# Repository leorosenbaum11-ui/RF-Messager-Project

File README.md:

# RF-Messager-Project
Radio Project using Micrf110ymm and Micrf220ayqs to recieve and transmit character data to an LCD screen. Working on code(Python), and fabrication. Also working on integrated or USB keyboard functionality.

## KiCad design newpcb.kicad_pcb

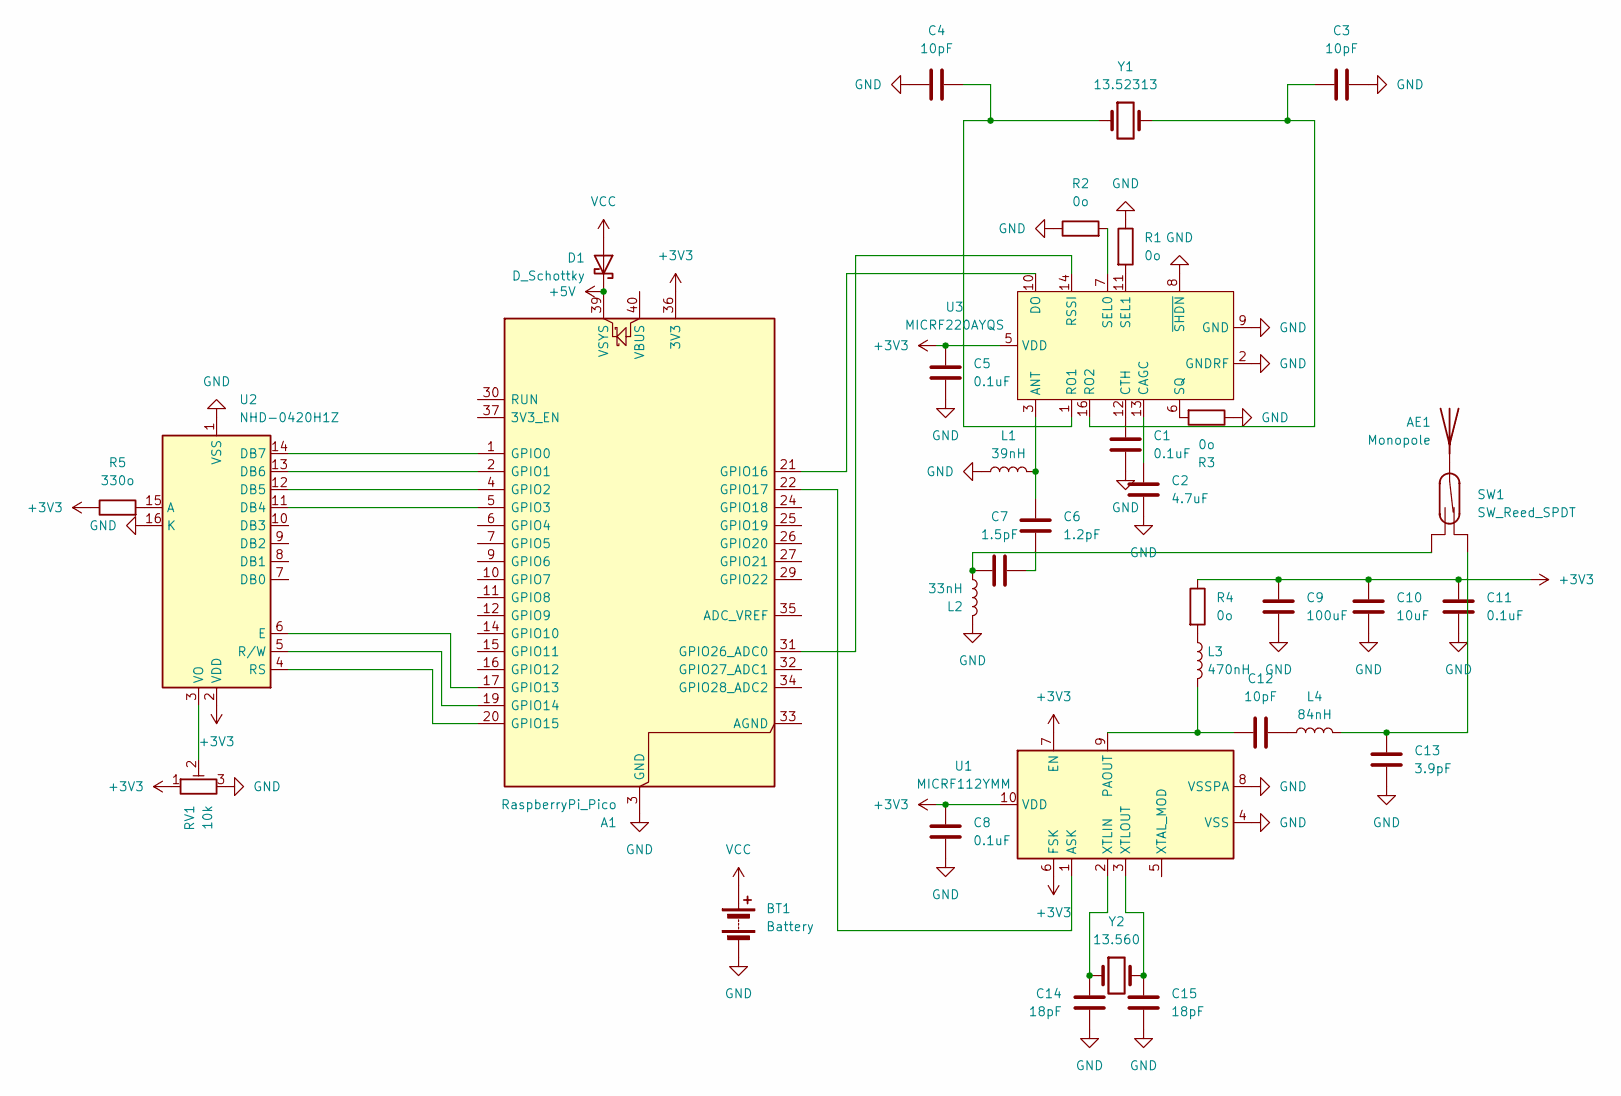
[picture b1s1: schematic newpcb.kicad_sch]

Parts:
A1: RaspberryPi_Pico; RaspberryPi_Pico_Common_Unspecified
AE1: Monopole; 433_92hz_Helical_Monopole_Inprogress
BT1: Battery; BatteryHolder_Bulgin_BX0034_1xAAA
C1, C5, C8, C11: 0.1uF; C_0603_1608Metric_Pad1.08x0.95mm_HandSolder
C2: 4.7uF; C_0603_1608Metric_Pad1.08x0.95mm_HandSolder
C3, C4, C12: 10pF; C_0603_1608Metric_Pad1.08x0.95mm_HandSolder
C6: 1.2pF; C_0603_1608Metric_Pad1.08x0.95mm_HandSolder
C7: 1.5pF; C_0603_1608Metric_Pad1.08x0.95mm_HandSolder
C9: 100uF; CP_Radial_D6.3mm_P2.50mm
C10: 10uF; C_0603_1608Metric_Pad1.08x0.95mm_HandSolder
C13: 3.9pF; C_0603_1608Metric_Pad1.08x0.95mm_HandSolder
C14, C15: 18pF; C_0603_1608Metric_Pad1.08x0.95mm_HandSolder
D1: D_Schottky; D_DO-41_SOD81_P10.16mm_Horizontal
L1: 39nH; L_0603_1608Metric_Pad1.05x0.95mm_HandSolder
L2: 33nH; L_0603_1608Metric_Pad1.05x0.95mm_HandSolder
L3: 470nH; L_0603_1608Metric_Pad1.05x0.95mm_HandSolder
L4: 84nH; L_0603_1608Metric_Pad1.05x0.95mm_HandSolder
R1, R2, R3, R4: 0o; R_0603_1608Metric_Pad0.98x0.95mm_HandSolder
R5: 330o; R_0603_1608Metric_Pad0.98x0.95mm_HandSolder
RV1: 10k; Potentiometer_Bourns_3296W_Vertical
SW1: SW_Reed_SPDT; Nidec_Copal_CAS-120A
U1: MICRF112YMM; MSOP-10_3x3mm_P0.5mm
U2: NHD-0420H1Z
U3: MICRF220AYQS; QSOP-16_3.9x4.9mm_P0.635mm
Y1: 13.52313; Crystal_SMD_0603-2Pin_6.0x3.5mm_HandSoldering
Y2: 13.560; Crystal_SMD_0603-2Pin_6.0x3.5mm_HandSoldering

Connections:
+3V3: A1.36 (3V3), C5.1, C8.1, C9.1, C10.1, C11.1, R4.1, R5.1, RV1.1, U1.6 (FSK), U1.7 (EN), U1.10 (VDD), U2.2 (VDD), U3.5 (VDD)
+5V: A1.39 (VSYS), D1.1 (K)
GND: A1.3 (GND), A1.8 (GND), A1.13 (GND), A1.18 (GND), A1.23 (GND), A1.28 (GND), A1.38 (GND), BT1.2 (-), C1.2, C2.2, C3.2, C4.1, C5.2, C8.2, C9.2, C10.2, C11.2, C13.2, C14.2, C15.2, L1.1, L2.2, R1.1, R2.1, R3.1, RV1.3, U1.4 (VSS), U1.8 (VSSPA), U2.1 (VSS), U2.16 (K), U3.2 (GNDRF), U3.4 (GNDRF), U3.8 (~SHDN), U3.9 (GND)
unnamed: A1.1 (GPIO0), U2.14 (DB7)
unnamed: A1.2 (GPIO1), U2.13 (DB6)
unnamed: A1.4 (GPIO2), U2.12 (DB5)
unnamed: A1.5 (GPIO3), U2.11 (DB4)
unnamed: A1.17 (GPIO13), U2.6 (E)
unnamed: A1.19 (GPIO14), U2.5 (R/W)
unnamed: A1.20 (GPIO15), U2.4 (RS)
unnamed: A1.21 (GPIO16), U3.10 (DO)
unnamed: A1.22 (GPIO17), U1.1 (ASK)
unnamed: A1.31 (GPIO26_ADC0), U3.14 (RSSI)
unnamed: AE1.1 (A_1), SW1.2
unnamed: C6.1, C7.2
unnamed: C7.1, L2.1, SW1.3
unnamed: C12.2, L4.1
unnamed: C13.1, L4.2, SW1.1
unnamed: L3.1, R4.2
unnamed: C12.1, L3.2, U1.9 (PAOUT)
unnamed: C14.1, U1.2 (XTLIN), Y2.1
unnamed: C15.1, U1.3 (XTLOUT), Y2.2
unnamed: R5.2, U2.15 (A)
unnamed: RV1.2, U2.3 (VO)
unnamed: C6.2, L1.2, U3.3 (ANT)
unnamed: C2.1, U3.13 (CAGC)
unnamed: C1.1, U3.12 (CTH)
unnamed: C4.2, U3.1 (RO1), Y1.1
unnamed: C3.1, U3.16 (RO2), Y1.2
unnamed: R2.2, U3.7 (SEL0)
unnamed: R1.2, U3.11 (SEL1)
unnamed: R3.2, U3.6 (SQ)
VCC: BT1.1 (+), D1.2 (A)

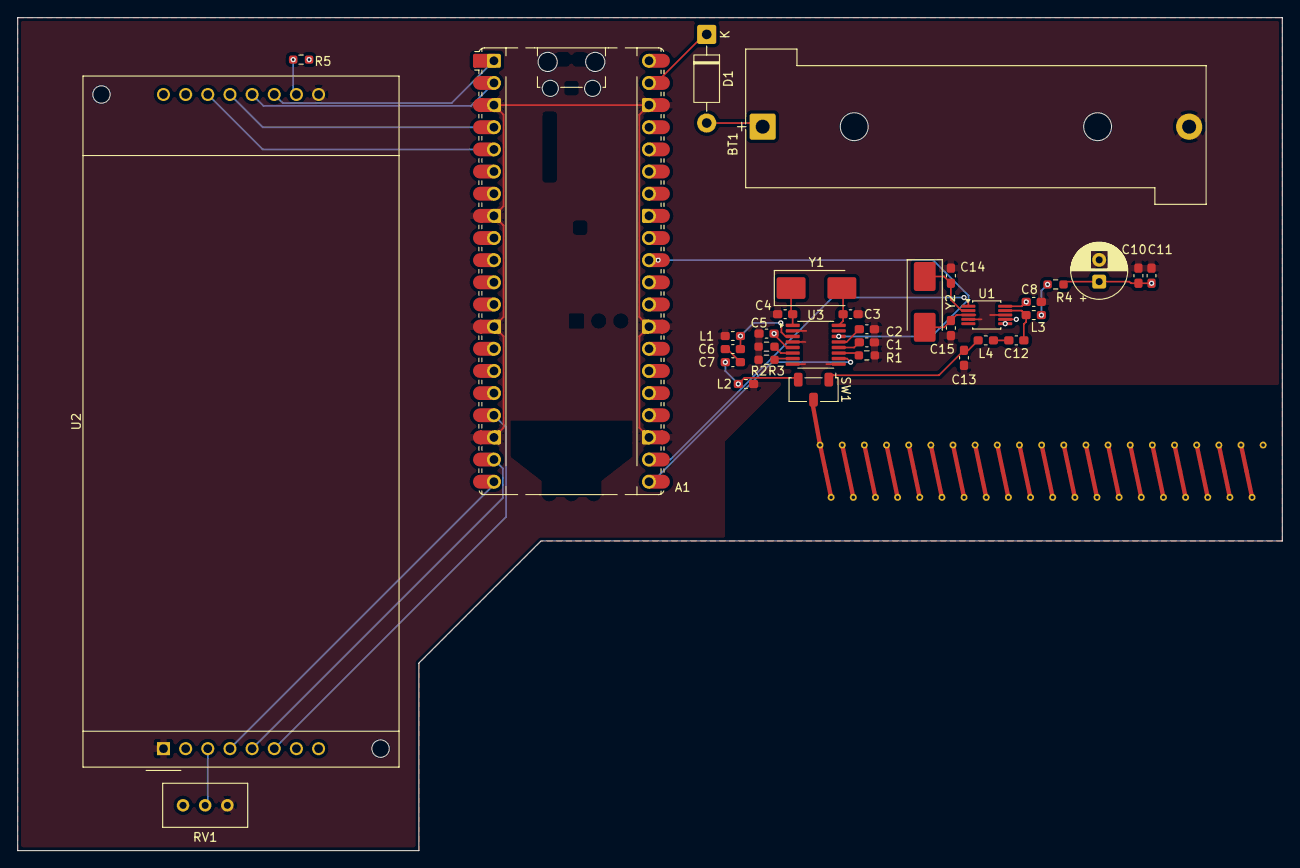
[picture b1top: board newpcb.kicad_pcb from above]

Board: 2 copper layers, 145.0 x 95.5 mm, 35 parts (0 on the bottom side), 33 nets.

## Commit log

2026-04-21 Add Kicad Files
2026-05-01 Drafted encryption, transmission and recieving, packet formation, and more
2026-05-02 Refactor RF encoding classes and improve receiver logic
2026-05-02 Debugging
    Refactor RF encoding and decoding classes to improve functionality and fix bugs.
2026-05-02 renamed so pico can access
2026-05-02 Made functional 🎉, optimized logic
2026-05-10 Add multi character input
2026-05-10 Create mainExperimental.py for non-functional experimental changes
2026-05-10 Add experimental code
2026-05-19 Add rf support and fixes and a bunch of stuff
2026-05-27 Add packet integrity stuff for long range, will add some more security variables soon
2026-05-27 Added security, variables for sending, variable footprint length and sample rate
2026-05-27 Security patch, add more variables, working wireless
2026-06-11 Added breakdown of encryption
